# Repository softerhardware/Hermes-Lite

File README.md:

Hermes-Lite 1.x Deprecated Project!!!
=====================================

This project is deprecated. Current development is now focussed on the Hermes-Lite 2.x. See the main [Hermes-Lite Web Page](http://www.hermeslite.com) for the latest links and details.

## Introduction

The hardware is based on Analog Devices' [AD9866](http://www.analog.com/en/broadband-products/broadband-codecs/ad9866/products/product.html) which is a 12-bit broadband modem mixed signal front end that has been repurposed as a direct down conversion and direct up conversion SDR transceiver covering 0-36 MHz. A hardware prototype has been built and tested that uses a [BeMicro SDK](http://www.arrownac.com/solutions/bemicro-sdk/) FPGA board for DSP processing. The FPGA firmware is a port of the [Hermes SDR](http://openhpsdr.org/wiki/index.php?title=HERMES) project. The ported firmware preserves enough compatibility with the original Hermes SDR so that existing Hermes front-end software may be used with the Hermes-Lite without modification. Initial receive and transmit tests show good performance and appear later in this README. All software and hardware intellectual property is open source. Contributions and derivatives are encouraged. Please follow the standard ["Fork and Pull"](https://help.github.com/articles/using-pull-requests/) model and introduce yourself on [Google Groups](https://groups.google.com/forum/#!forum/hermes-lite).

#### Project Goals
 * 0-30MHz (HF) transceiver with decent performance
 * Entirely open source and open hardware design
 * Cost of less than $150 (cost includes FPGA board) for hobbyist who build their own
 * Maintain enough compatibility with Hermes to use existing Hermes SDR front-end software with no or minor modification

#### Hermes-Lite v1.21

#### Hermes-Lite v1.2

#### Hermes-Lite v0.9

## Receive Experiments

I compared the Hermes-Lite with a Hermes and a [SoftRock RXTX Ensemble Transceiver](http://fivedash.com/) at spotting JT65 and JT9 transmissions with [WSJT-X](http://www.physics.princeton.edu/pulsar/K1JT/wsjtx.html) software running on Linux. I connected two radios to the same antenna right at a tee so there is no additional coax for either radio. I adjusted the radios so that common spots are within a few Hz. This ensures that one radio is not spotting signals that are out of band for the other. I adjusted audio levels to be similar for both copies of WSJT-X that I am running. WSJT-X is not very sensitive to different input levels anyway. The Hermes and Hermes-Lite were both using [ghpsdr-alex](http://napan.ca/ghpsdr3/index.php/Main_Page) software running on separate computers, and the RXTX was using [Quisk](http://james.ahlstrom.name/quisk/). The Hermes has a 4-1 impedance transformer. The Hermes-Lite has a 9-1 impedance transformer to better match the 400 Ohm input of the AD9866. This explains some differences in the data. The Hermes was run with no attenuation and hence has 20 dB gain from the LTC6400-20. The Hermes-Lite was also run with integrated gain set to ~20 dB unless noted otherwise. Finally, I let everything run for several hours to get a large sample set. 

### JT65 and JT9 Spot Data

| Band | 30M | 30M | 30M | 10M | 10M | 10M | 10M | 10M |
|:---- | ---:| ---:| ---:| ---:| ---:| ---:| ---:| ---:|
| Total Spots | 1629  |  676  |  826  |  2421  |  1488  |  1934  |  2461  |  570  |
| Common Spots | 1448 (88.9%)  |  647 (95.7%)  |  792 (95.9%)  |  1680 (69.4%)  |  778 (52.3%)  |  1420 (73.4%)  |  1663 (67.6%)  |  414 (72.6%)  |
| Lite Unique Spots |  |  22 (3.3%)  |  24 (2.9%)  |  |  699 (47.0%)  |  493 (25.5%)  |  768 (31.2%)  |  39 (6.8%)  |
| Hermes Unique Spots |  103 (6.3%)  |  7 (1.0%)  |  10 (1.2%)  |  342 (14.1%)  | |  21 (1.1%)  |  30 (1.2%)  |  117 (20.5%)  |
| RXTX Unique Spots |   78 (4.8%)  | | |  399 (16.5%)  |  11 (0.7%)  | | | |
| Lite Gain dB | | 20  | 28  | | 28  | 20  | 28  | 12  |
| Lite Common SNR Average dB |  |  -8.1   |  -7.7   | | -4.7 |  -9.0  |  -9.1   |  -12.8   |
| Hermes Common SNR Average dB | -7.3   |  -8.0   |  -7.7   |  -6.1   | |  -9.8   |  -10.2   |  -9.6   |
| RXTX Common SNR Average dB |  -7.5   | | |  -10.0   |  -12.6   |  | |  |
| Lite Unique SNR Average dB | |  -11.9   |  -11.5   |  |  -17.3   |  -16.2   |  -14.8   |  -15.5   |
| Hermes Unique SNR Average dB |  -15.3   |  -13.3   |  -20.4   |  -16.9   | |  -16.0   |  -14.2   |  -18.5   |
| RXTX Unique SNR Average dB |  -8.6   | | |  -11.9   |  -12.0   | | | |

The results from the Hermes-Lite compare well with the Hermes and the RXTX. You can see that on 30M all radios were about the same, maybe with a slight edge to the Hermes-Lite on unique spot count. The more interesting data is on 10M. Here there was a clear advantage to the Hermes-Lite in terms of unique spots and SNR (average SNR of all common spots) when the Hermes-Lite was run at 20 dB gain (to match the fixed gain of the Hermes but not accounting for the different input transformers) or 28 dB. When the Hermes-Lite was run with only 12 dB gain, the Hermes did better. This suggests that the Hermes might benefit from additional gain on the higher frequencies.  

When one radio has a unique spot that the other misses, it is not because the other radio missed all spots within that minute. Rather, I see that one radio spots n and the other n-1. The missed spot is not always the weakest signal. Sometimes it is a fairly strong signal. More often the missed spot is a JT9 signal, which has a narrower bandwidth and more stringent demands.

I did not experience problems with exceeding the lower dynamic range of the Hermes-Lite. This may be due in part to my relatively poor antenna setup and rural town location. All experiments were with a ~7M vertical with base at ~2M above ground with a wire grape trellis as a ground plane. The vertical was tuned with a Z-match at the base. Also, the integrated gain in the Hermes-Lite with control in 1 dB steps from -12 dB to +48 dB appears useful to extend the dynamic range. There is a fast path to adjust this gain so that an AGC may be implemented.

These experiments only test a receiver's performance at decoding JT65 and JT9 in the real world, and other proper receiver measurments should be run, but I think they are somewhat indicative of a receiver's performance in general. Even though a less expensive ADC and clock source were used when compared to the Hermes, I did not see any dramatic penalty in reception of JT65 and JT9 spots. Instead, I saw cases where the Hermes-Lite performed better. 

## Transmit Experiments

I tested transmit with [WSPR](http://www.physics.princeton.edu/pulsar/K1JT/wspr.html) and observed spots of my signal on [WSPRnet](http://wsprnet.org/). [PowerSDR](http://openhpsdr.org/wiki/index.php?title=PowerSDR) running under Windows was used to test transmit. At first, I had only 10 dBm (10 mW) output as I had not adjusted the transmit interpolation filter for the new sampling frequency. After adjusting the interpolation filter, I had 17 dBm (50 mW) output. I am using the IAMP on the AD9866 which will do 20 dBm (100 mW) and even 23 dBm (200 mW) with some distortion. I am targeting 20 dBm (100 mW) but need to get a large ferrite core to accomodate the correct turns ratio. The unique WSPR spots appear below. This is just an indicator that transmit is working and proper transmit measurments still must be made.

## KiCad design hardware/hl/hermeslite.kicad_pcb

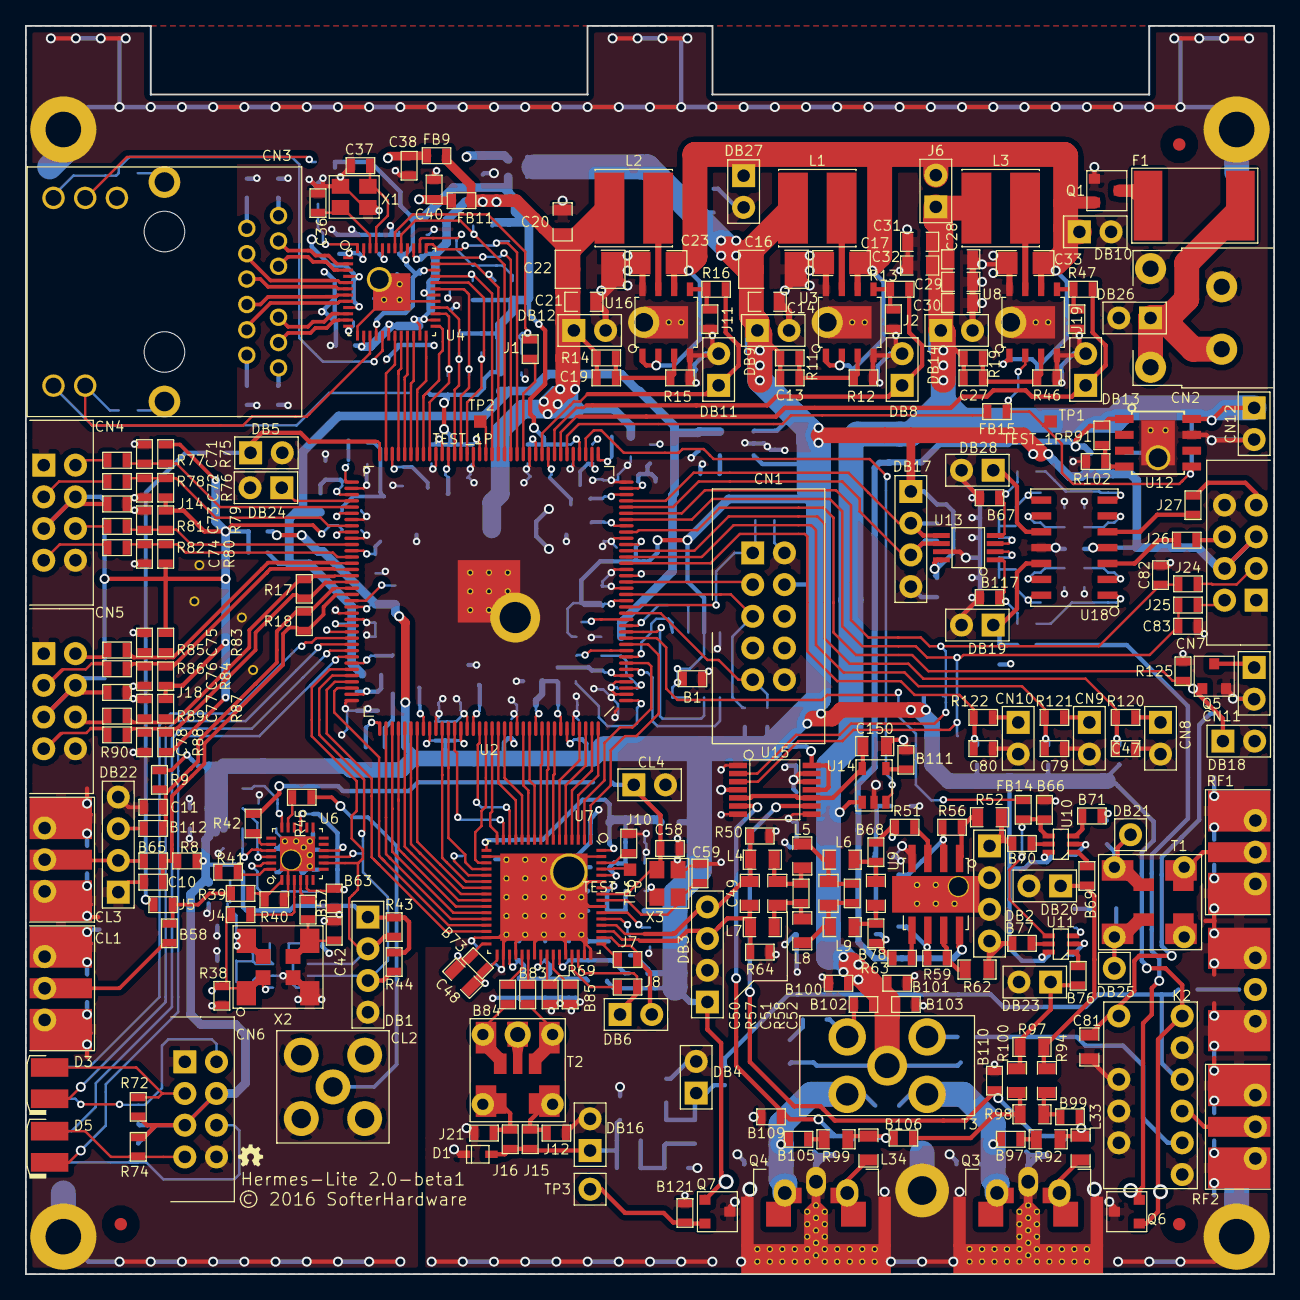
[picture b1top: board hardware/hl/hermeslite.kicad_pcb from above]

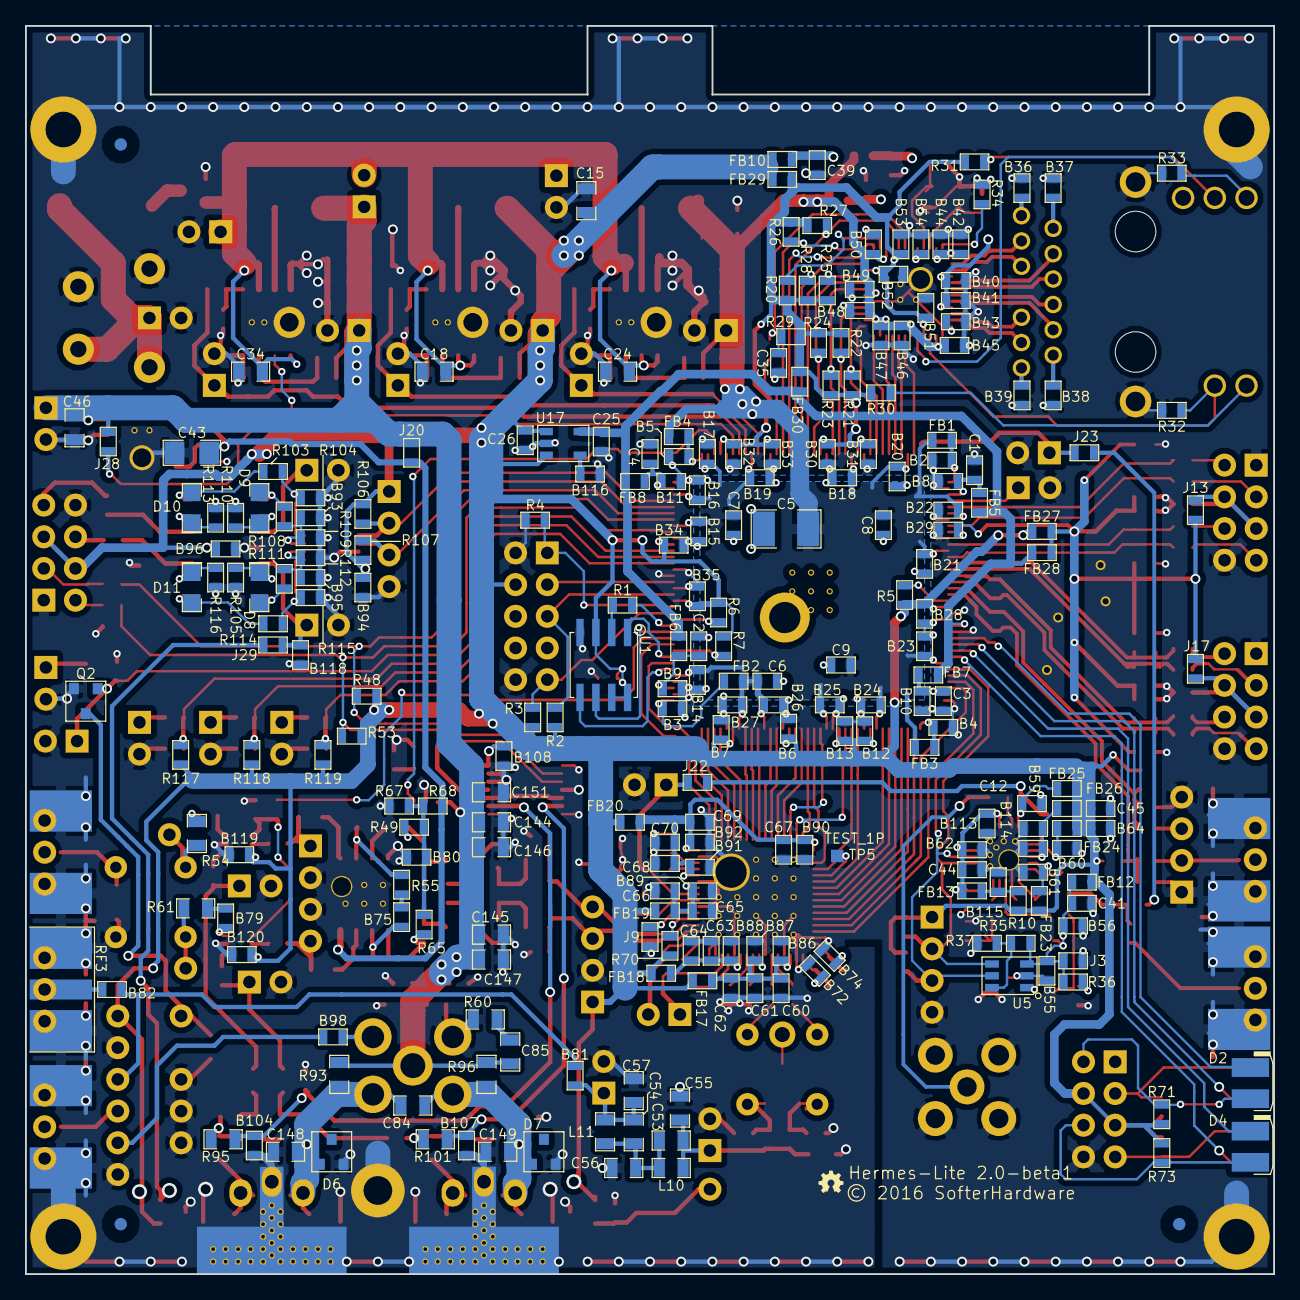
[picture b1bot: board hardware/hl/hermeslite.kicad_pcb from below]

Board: 4 copper layers, 100.0 x 100.0 mm, 514 parts (248 on the bottom side), 289 nets.

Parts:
B1, B2, B3, B4, B5, B6, B7, B8, B9, B10, B11, B12, B13, B14, B15, B16, B17, B18, B19, B20, B21, B22, B23, B24, B25, B26, B27, B28, B29, B30, B31, B32, B33, B34, B35, B36, B37, B38, B39, B40, B41, B42, B43, B44, B45, B46, B47, B48, B49, B50, B51, B52, B53, B54, B55, B56, B57, B58, B59, B60, B61, B62, B63, B64, B65, B66, B67, B68, B69, B70, B71, B72, B73, B74, B75, B76, B77, B78, B79, B80, B81, B82, B83, B84, B85, B86, B87, B88, B89, B90, B91, B92, B93, B94, B95, B96, B97, B98, B99, B100, B101, B102, B103, B104, B105, B106, B107, B108, B109, B110, B111, B112, B113, B114, B115, B116, B117, B119, B120: 0.1uF; SMD-0603
B118, B121: DNI; SMD-0603
C1, C2, C3, C4, C6, C7, C8, C9, C12, C25, C35, C38, C39, C40, C41, C44, C45, C62, C64, C66, C70: 10uF; SMD-0603
C5, C16, C22: 100uF; SMD-1210
C10, C11, C26, C47, C60, C61, C63, C65, C67, C68, C69, C71, C72, C73, C74, C75, C76, C77, C78, C79, C80: 1uF; SMD-0603
C13, C19, C27: 4.7nF; SMD-0603
C14, C15, C20, C21, C28, C29, C30, C31, C32: 22uF; SMD-0805
C17, C23, C33, C43: 10uF; SMD-1206
C18, C24, C34: 4.7uF; SMD-0805
C36, C37, C58, C59: 15pF; SMD-0603
C42, C82, C83: DNI; SMD-0603
C46, C144, C145, C146, C147, C151: 1uF; SMD-0805
C48, C150: 10uF; SMD-0805
C49: 75pF; SMD-0805
C50: 150pF; SMD-0805
C51: 160pF; SMD-0805
C52, C55, C57, C81: 100pF; SMD-0805
C53: 10pF; SMD-0805
C54, C85, C148, C149: DNI; SMD-0805
C56: 180pF; SMD-0805
C84: 270pF; SMD-0805
CL1, CL3: SMA; SMAEDGE_TH
CL2: SMA; SMAVERT
CL4: RFD2b; 2x1
CN1: USBBlaster2; USBBLASTER
CN2: PS; POWERPP
CN3: MagJack; MAGJACK
CN4, CN5, CN6, CN7: IO8; IO
CN8, CN9, CN10, CN11, CN12: RFD2b; 2x1
D1: TVS; SOD323
D2, D3, D4, D5: Led_Small; LED
D6, D7: DNI; SOT23_3
D8, D9, D10, D11: 1N5711; 1N5711WS
DB1, DB2, DB3: RFD4d; 4x1
DB4, DB5, DB16: RFD2a; 2x1
DB6, DB8, DB9, DB10, DB11, DB12, DB13, DB14, DB18, DB19, DB20, DB23, DB24, DB26, DB27, DB28: RFD2b; 2x1
DB17: RFD4b; 4x1
DB21, DB25: TEST_1P; 1x1
DB22: RFD4f; 4x1
F1: 3A@20V; FUSE
FB1, FB2, FB3, FB4, FB5, FB6, FB7, FB8, FB9, FB10, FB11, FB12, FB13, FB14, FB15, FB17, FB18, FB19, FB20, FB23, FB24, FB25, FB26, FB27, FB30: FB; SMD-0603
FB28, FB29: DNI; SMD-0603
FIDUCIAL: VAL**; FIDUCIAL
FIDUCIAL#2, FIDUCIAL#3, FIDUCIAL#4, FIDUCIAL#5, FIDUCIAL#6: VAL**; FIDUCIAL
GT1, GT2, GT3, GT4: TEST_1P; GNDTAP
J1, J2, J9, J10, J11, J14, J15, J18, J19, J20, J21, J22, J24, J25, J26, J27, J29: JNC; SMD-0603
J3, J4, J5, J7, J8, J12, J13, J16, J17, J23, J28: JNO; SMD-0603
J6: DNI; 2x1
K2: NA3WK-K; DPDT_GND
L1, L3: 3.3uH; GENERICPSL
L2: 2.2uH; GENERICPSL
L4, L7: 240nH; SMD-0805
L5, L6, L8, L9: 270nH; SMD-0805
L10, L11: 330nH; SMD-0805
L33, L34: 0nH; SMD-0805
MH1, MH2, MH3, MH4: TEST_1P; m2p5
MH5: TEST_1P; m2p0
Q1: DMP3099L; SOT23_3
Q2: NUD3124; SOT23_3
Q3, Q4: LDMOS; COMBORF
Q5: 2N7002K; SOT23_3
Q6, Q7: MCP9700; SOT23_3
R1, R42, R45, R50, R64: 33; SMD-0603
R2, R3, R4, R5, R6, R7, R8, R9, R15, R21, R22, R23, R24, R25, R27, R28, R29, R37, R70, R75, R76, R79, R80, R83, R84, R87, R88, R117, R118, R119: 10K; SMD-0603
R10: 2.2; SMD-0603
R11: 35.7K; SMD-0603
R12: 11.5K; SMD-0603
R13, R16, R17, R18, R36, R38, R41, R47, R125: DNI; SMD-0603
R14: 20K; SMD-0603
R19: 16.2K; SMD-0603
R20, R26, R49, R65: 2.2K; SMD-0603
R30, R31: 270; SMD-0603
R32, R33, R57, R58, R67, R68, R103, R108, R111, R114: 1K; SMD-0603
R34, R91: 12.1K; SMD-0603
R35: 3.3K; SMD-0603
R39: 120; SMD-0603
R40, R55: 75; SMD-0603
R43, R44, R48, R53, R106, R107: 4.7K; SMD-0603
R46: 1.5K; SMD-0603
R51, R63: 22; SMD-0603
R52, R62: 10; SMD-0805
R54, R61, R94, R100: 14; SMD-0805
R56, R59, R71, R72, R73, R74, R77, R78, R81, R82, R85, R86, R89, R90, R120, R121, R122: 330; SMD-0603
R60, R93, R96, R97, R98: DNI; SMD-0805
R69, R102: 1.6K; SMD-0603
R92, R99: 270; SMD-0805
R95, R101: 1K; SMD-0805
R104, R109, R112, R115: 1.8K; SMD-0603
R105, R110, R113, R116: 220K; SMD-0603
RF1, RF2, RF3: BNC; SMAEDGE_TH
T1: 1:1 Z; TRANSFSMT4
T2: 8:1 Z; TRANSFSMT
T3: TRANSF4CTS; BN202V
TP1, TP2, TP5, TP6: TEST_1P; TP
TP3: TEST_1P; 1x1
U1: EEPROM; SOIC-8
U2: FPGA; CYCLONEIV
U3, U8, U16: ST1S10
U4: KSZ9031RN; KSZ9031
U5: MCP4716
U6: 5P49V5923; IDTVERSA
U7: AD9866BCPZ; AD9866
U9: OPA2677
U10, U11: PE4259
U12: AP2204; ap2204
U13: MAX11613
U14: LP2985; SOT23
U15: MCP4661
U17: TPS730; SOT23
U18: LMV324
X1: 25MHz; XTAL
X2: 38.4MHz; MULTIOSC
X3: 38.4MHz; XTAL

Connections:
+1V2: B14.1, B15.1, B16.1, B17.1, B18.1, B19.1, B20.1, B21.1, B22.1, B23.1, B24.1, B25.1, B26.1, B27.1, B45.1, B46.1, B47.1, B48.1, B49.1, B50.1, C5.2, C6.2, C7.2, C8.2, C9.2, C19.1, C20.1, C21.1, C22.1, DB12.1, FB1.1, FB2.1, FB3.1, FB4.1, FB9.1, FB11.1, L2.2, R14.1, U2.5, U2.29, U2.34, U2.38, U2.45, U2.61, U2.70, U2.78, U2.84, U2.102, U2.116, U2.124, U2.134, U2.138, U4.14, U4.18, U4.23, U4.26, U4.30, U4.39
+2V5: C25.1, FB5.1, FB6.1, FB7.1, FB8.1, FB28.1, FB30.1, U2.96, U17.5
+3V3: B1.1, B6.1, B7.1, B12.1, B13.1, B28.1, B34.1, B35.1, B64.1, B94.1, B96.1, B108.1, B119.1, B120.1, C13.1, C14.1, C15.1, C16.1, C26.1, C45.1, CN1.4, CN6.4, CN6.5, CN7.4, CN7.5, DB1.1, DB3.1, DB9.1, DB17.1, FB10.2, FB12.2, FB17.2, FB18.1, FB19.1, FB20.2, FB23.2, FB24.2, FB25.2, FB26.2, FB27.1, FB29.1, K2.1, L1.2, Q6.1, Q7.1, R2.2, R3.2, R5.2, R6.2, R7.2, R8.2, R9.2, R10.1, R11.1, R43.2, R44.2, R48.2, R53.2, R70.2, R71.2, R72.2, R73.2, R74.2, R106.2, R107.2, R117.2, R118.2, R119.2, U1.3, U1.7, U1.8, U2.17, U2.26, U2.93, U2.117, U2.122, U2.130, U2.139, U10.6, U11.6, U13.8, U15.11, U15.14, U17.1, U17.3, U18.4
+VOP: C43.1, J20.2, R68.2, R91.1, U9.8, U12.1
+VPA: B100.2, B101.2, B102.2, B103.2, C27.1, C28.1, C29.1, C30.1, C31.1, C32.1, C46.1, C85.2, C144.1, C145.1, C146.1, C147.1, C151.1, CN12.1, DB14.1, J6.1, J20.1, J28.1, L3.2, R19.1, R93.1, R96.2, T3.2, U12.8, U14.1
/Clock/SCL1: DB1.3, R44.1, U2.104, U5.5, U6.9
/Clock/SDA1: DB1.2, R43.1, U2.103, U5.4, U6.8
/Ethernet/RXD0: R24.2, U2.58, U4.32
/Ethernet/RXD1: R23.2, U2.59, U4.31
/Ethernet/RXD2: R22.2, U2.60, U4.28
/Ethernet/RXD3: R21.2, U2.64, U4.27
/Ethernet/TXD0: U2.71, U4.19
/Ethernet/TXD1: U2.69, U4.20
/Ethernet/TXD2: U2.68, U4.21
/Ethernet/TXD3: U2.67, U4.22
/Input Output/AIN1: J26.1, U18.3
/Input Output/AIN2: J27.1, U18.5
/PA/TR: DB18.1, Q2.1, Q5.1, R125.2, U2.28
/PA/bias0: B104.2, B110.1, R95.2, U15.9
/PA/bias1: B107.2, B109.1, R101.2, U15.6
/RF Frontend/Vop/2: B80.2, R49.1, R65.2, R67.2, R68.1
GND: B1.2, B2.2, B3.2, B4.2, B5.2, B6.2, B7.2, B8.2, B9.2, B10.2, B11.2, B12.2, B13.2, B14.2, B15.2, B16.2, B17.2, B18.2, B19.2, B20.2, B21.2, B22.2, B23.2, B24.2, B25.2, B26.2, B27.2, B28.2, B29.2, B30.2, B31.2, B32.2, B33.2, B34.2, B35.2, B36.2, B37.2, B38.2, B39.2, B40.2, B41.2, B42.2, B43.2, B44.2, B45.2, B46.2, B47.2, B48.2, B49.2, B50.2, B51.2, B52.2, B53.2, B54.2, B55.2, B56.2, B59.2, B60.2, B61.2, B62.2, B63.2, B64.2, B66.1, B67.2, B72.2, B74.2, B80.1, B85.2, B86.2, B87.2, B88.2, B89.2, B90.2, B91.2, B92.2, B93.2, B94.2, B95.2, B96.2, B100.1, B101.1, B102.1, B103.1, B104.1, B107.1, B108.2, B109.2, B110.2, B111.2, B113.2, B114.2, B115.2, B116.2, B117.2, B118.2, B119.2, B120.2, B121.2, C1.2, C2.2, C3.2, C4.2, C5.1, C6.1, C7.1, C8.1, C9.1, C10.2, C11.2, C12.2, C14.2, C15.2, C16.2, C17.2, C18.2, C20.2, C21.2, C22.2, C23.2, C24.2, C25.2, C26.2, C28.2, C29.2, C30.2, C31.2, C32.2, C33.2, C34.2, C35.2, C36.2, C37.2, C38.2, C39.2, C40.2, C41.2, C42.1, C43.2, C44.2, C45.2, C46.2, C47.2, C55.2, C56.2, C57.2, C58.2, C59.2, C60.2, C61.2, C62.2, C63.2, C64.2, C65.2, C66.2, C67.2, C68.2, C69.2, C70.2, C71.2, C72.2, C73.2, C74.2, C75.2, C76.2, C77.2, C78.2, C79.2, C80.2, C81.2, C82.2, C83.2, C144.2, C145.2, C146.2, C147.2, C148.2, C149.2, C150.2, C151.2, CL1.2, CL2.2, CL3.2, CL4.2, CN1.2, CN1.10, CN2.2, CN3.18, CN4.1, CN4.8, CN5.1, CN5.8, CN6.1, CN6.8, CN7.1, CN7.8, CN8.2, CN9.2, CN10.2, CN11.2, CN12.2, D1.2, D6.2, D7.2, DB1.4, DB2.2, DB2.3, DB3.2, DB4.2, DB5.2, DB8.2, DB9.2, DB10.2, DB11.2, DB12.2, DB13.2, DB14.2, DB16.2, DB17.4, DB18.2, DB19.2, DB20.2, DB22.1, DB22.4, DB23.2, DB24.2, DB26.2, DB27.2, DB28.2, GT1.1, GT2.1, GT3.1, GT4.1, J2.1, J3.2, J9.1, J10.1, J11.1, J12.2, J14.1, J18.1, J19.1, J21.1, K2.2, K2.6, K2.8, K2.9, K2.10, MH1.1, MH2.1, MH3.1, MH4.1, MH5.1, Q1.1, Q2.2, Q3.2, Q4.2, Q5.2, Q6.3, Q7.3, R4.2, R12.2, R15.2, R32.2, R33.2, R34.2, R37.2, R38.2, R40.2, R46.2, R50.2, R60.1, R64.1, R67.1, R69.1, R102.1, R104.1, R105.2, R109.1, R110.2, R112.1, R113.2, R115.1, R116.2, R125.1, RF1.2, RF2.2, RF3.2, T1.3, T3.4, U1.4, U2.2, U2.4, U2.19, U2.21, U2.22, U2.27, U2.36, U2.41, U2.48, U2.57, U2.63, U2.74, U2.79, U2.82, U2.94, U2.95, U2.97, U2.108, U2.118, U2.123, U2.131, U2.140, U2.145, U3.4, U3.8, U3.9, U4.13, U4.29, U4.49, U5.2, U6.2, U6.25, U7.18, U7.31, U7.34, U7.36, U7.39, U7.44, U7.47, U7.48, U7.55, U7.59, U7.63, U7.65, U8.4, U8.8, U8.9, U9.4, U10.2, U11.2, U12.7, U13.7, U14.2, U15.1, U15.4, U15.7, U15.8, U15.12, U15.13, U16.4, U16.8, U16.9, U17.2, U18.11, X1.3, X2.2, X3.3
unnamed: B2.1, FB1.2, U2.73
unnamed: B3.1, FB2.2, U2.1
unnamed: B4.1, FB3.2, U2.109
unnamed: B5.1, FB4.2, U2.37
unnamed: B8.1, C1.1, FB5.2, U2.75
unnamed: B9.1, C2.1, FB6.2, U2.3
unnamed: B10.1, C3.1, FB7.2, U2.107
unnamed: B11.1, C4.1, FB8.2, U2.35
unnamed: B36.1, CN3.12
unnamed: B37.1, CN3.6
unnamed: B38.1, CN3.1
unnamed: B39.1, CN3.7
unnamed: B40.1, B41.1, C38.1, FB9.2, U4.4, U4.9
unnamed: B42.1, B43.1, B44.1, C39.1, FB10.1, U4.1, U4.12, U4.47
unnamed: B54.1, C40.1, FB11.2, U4.44
unnamed: B55.1, B56.1, C41.1, FB12.1, J3.1, R35.1, R36.1, U5.3, X2.4
unnamed: B57.1, C42.2, X2.3
unnamed: B57.2, U6.4
unnamed: B58.1, J5.1, R39.2
unnamed: B58.2, CL1.1
unnamed: B59.1, FB25.1, U6.18
unnamed: B60.1, FB24.1, U6.21
unnamed: B61.1, FB23.1, U6.23
unnamed: B65.1, CL3.1, DB22.2
unnamed: B65.2, C10.1, R8.1, R18.1, U2.91
unnamed: B66.2, FB14.1, U10.4, U11.4
unnamed: B67.1, R103.1, R104.2, U13.4
unnamed: B68.1, R49.2, R51.2
unnamed: B68.2, C52.1, L6.2
unnamed: B69.1, U10.1
unnamed: B70.1, U10.5
unnamed: B70.2, DB2.1, R52.1
unnamed: B71.1, U10.3
unnamed: B71.2, R54.2
unnamed: B72.1, B73.1, C48.1, U7.33
unnamed: B73.2, B74.1, C48.2, U7.32
unnamed: B75.1, R59.2, U9.6
unnamed: B75.2, R55.1
unnamed: B76.1, U11.1
unnamed: B77.1, U11.5
unnamed: B77.2, DB2.4, R62.1
unnamed: B78.1, R63.2, R65.1
unnamed: B78.2, C52.2, L9.1
unnamed: B79.1, U11.3
unnamed: B79.2, R61.2
unnamed: B81.2, C54.1, C57.1, DB4.1, L11.2
unnamed: B82.1, RF3.1
unnamed: B83.1, T2.1
unnamed: B83.2, U7.38
unnamed: B84.1, T2.3
unnamed: B84.2, U7.37
unnamed: B85.1, U7.42
unnamed: B86.1, B87.1, C60.1, C61.1, C62.1, FB17.1, U7.35, U7.40
unnamed: B88.1, C63.1, C64.1, FB18.2, U7.43
unnamed: B89.1, C65.1, C66.1, FB19.2, U7.58
unnamed: B90.1, B91.1, B92.1, C67.1, C68.1, C69.1, C70.1, FB20.1, U7.17, U7.60, U7.64
unnamed: B93.1, R108.1, R109.2, U13.3
unnamed: B95.1, R111.1, R112.2, U13.2
unnamed: B97.1, C84.1, C148.1, D6.1, Q3.3, R93.2, T3.1
unnamed: B97.2, R92.1
unnamed: B98.1, K2.5
unnamed: B98.2, T3.5
unnamed: B99.1, L33.1, R92.2, R95.1
unnamed: B99.2, R94.1, R98.2
unnamed: B105.1, C84.2, C149.1, D7.1, Q4.3, R96.1, T3.3
unnamed: B105.2, R99.1
unnamed: B106.1, L34.1, R99.2, R101.1
unnamed: B106.2, R98.1, R100.1
unnamed: B111.1, U14.4
unnamed: B112.1, DB22.3
unnamed: B112.2, C11.1, R9.1, R18.2, U2.90
unnamed: B62.1, B63.1, B113.1, C44.1, FB13.1, U6.5, U6.10, U6.15
unnamed: B114.1, C12.1, FB26.1, U6.22
unnamed: B115.1, FB13.2, R10.2
unnamed: B116.1, U17.4
unnamed: B117.1, R114.1, R115.2, U13.1
unnamed: B118.1, DB19.1, J29.2, U18.12
unnamed: B121.1, Q7.2, TP3.1
unnamed: C13.2, R11.2, R12.1, U3.3
unnamed: C17.1, C18.1, C23.1, C24.1, C33.1, C34.1, DB10.1, DB27.1, J6.2, Q1.2, U3.1, U3.2, U3.6, U8.1, U8.6, U16.1, U16.2, U16.6
unnamed: C19.2, R14.2, R15.1, U16.3
unnamed: C27.2, R19.2, R46.1, U8.3
unnamed: C35.1, J1.1, R29.1, U4.42
unnamed: C36.1, U4.46, X1.2
unnamed: C37.1, U4.45, X1.1
unnamed: C47.1, R117.1, R120.2, U2.25
unnamed: C49.1, DB3.4, L4.1, R50.1, U7.52
unnamed: C49.2, DB3.3, L7.2, R64.2, U7.51
unnamed: C50.1, L4.2, L5.1, R57.2
unnamed: C50.2, L7.1, L8.2, R57.1
unnamed: C51.1, L5.2, L6.1, R58.2
unnamed: C51.2, L8.1, L9.2, R58.1
unnamed: C53.1, C54.2, C56.1, L10.2, L11.1
unnamed: C53.2, C55.1, D1.1, DB16.1, J15.2, J16.1, L10.1
unnamed: C58.1, CL4.1, J22.2, U7.57, X3.2
unnamed: C59.1, U7.56, X3.1
unnamed: C71.1, R75.1, R77.1, U2.77
unnamed: C72.1, R76.1, R78.1, U2.80
unnamed: C73.1, R79.1, R81.1, U2.83
unnamed: C74.1, R80.1, R82.1, U2.85
unnamed: C75.1, R83.1, R85.1, U2.86
unnamed: C76.1, R84.1, R86.1, U2.87
unnamed: C77.1, R17.1, R87.1, R89.1, U2.88
unnamed: C78.1, R17.2, R88.1, R90.1, U2.89
unnamed: C79.1, R118.1, R121.2, U2.24
unnamed: C80.1, R119.1, R122.2, U2.23
unnamed: C81.1, K2.12, Q2.3
unnamed: C85.1, R60.2
unnamed: C150.1, U14.5, U15.5, U15.10
unnamed: CL2.1, R45.1
unnamed: CN1.1, R4.1, U2.16
unnamed: CN1.3, U2.20
unnamed: CN1.5, R2.1, U2.18
unnamed: CN1.9, R3.1, U2.15
unnamed: CN2.1, DB26.1, F1.1
unnamed: CN3.2, U4.8
unnamed: CN3.3, U4.7
unnamed: CN3.4, U4.6
unnamed: CN3.5, U4.5
unnamed: CN3.8, U4.11
unnamed: CN3.9, U4.10
unnamed: CN3.10, U4.3
unnamed: CN3.11, U4.2
unnamed: CN3.13, R32.1, U4.15
unnamed: CN3.14, R30.1
unnamed: CN3.16, R31.1
unnamed: CN3.17, R33.1, U4.17
unnamed: CN4.2, R77.2
unnamed: CN4.3, R78.2
unnamed: CN4.4, CN4.5, J13.2, J14.2
unnamed: CN4.6, R81.2
unnamed: CN4.7, R82.2
unnamed: CN5.2, R85.2
unnamed: CN5.3, R86.2
unnamed: CN5.4, CN5.5, J17.2, J18.2
unnamed: CN5.6, R89.2
unnamed: CN5.7, R90.2
unnamed: CN6.2, D2.2, R71.1
unnamed: CN6.3, D3.2, R72.1
unnamed: CN6.6, D4.2, R73.1
unnamed: CN6.7, D5.2, R74.1
unnamed: CN7.2, J25.2
unnamed: CN7.3, J24.2
unnamed: CN7.6, J26.2
unnamed: CN7.7, J27.2
unnamed: CN8.1, R120.1
unnamed: CN9.1, R121.1
unnamed: CN10.1, R122.1
unnamed: CN11.1, Q5.3
unnamed: D2.1, U2.98
unnamed: D3.1, U2.99
unnamed: D4.1, U2.100
unnamed: D5.1, U2.101
unnamed: D8.1, R111.2, U18.14
unnamed: D8.2, R105.1, U18.13
unnamed: D9.1, R108.2, U18.8
unnamed: D9.2, R110.1, U18.9
unnamed: D10.1, R103.2, U18.7
unnamed: D10.2, R113.1, U18.6
unnamed: D11.1, R114.2, U18.1
unnamed: D11.2, R116.1, U18.2
unnamed: DB5.1, J23.2, U2.72
unnamed: DB6.1, J8.1, U7.46
unnamed: DB6.2, J7.1, U7.50
unnamed: DB8.1, R13.2, U2.44
unnamed: DB11.1, R16.2, U2.46
unnamed: DB13.1, R47.2, U2.43
unnamed: DB17.2, R106.1, U2.33, U13.5
unnamed: DB17.3, R107.1, U2.32, U13.6
unnamed: DB21.1, R54.1, T1.1
unnamed: DB24.1, U2.76
unnamed: DB25.1, R61.1, T1.2
unnamed: DB28.1, U18.10
unnamed: F1.2, Q1.3
unnamed: FB14.2, U2.11
unnamed: FB15.1, U2.42
unnamed: FB15.2, J28.2, TP1.1, U8.2, U12.5
unnamed: J1.2, U2.49
unnamed: J2.2, R13.1, U3.5
unnamed: J4.1, R36.2, R38.1, U5.1, X2.1
unnamed: J4.2, U6.3
unnamed: J7.2, U7.49
unnamed: J8.2, U7.45
unnamed: J9.2, U7.54
unnamed: J10.2, U7.62
unnamed: J11.2, R16.1, U16.5
unnamed: J12.1, J15.1, T2.5
unnamed: J16.2, J21.2, T2.4
unnamed: J19.2, R47.1, U8.5
unnamed: J5.2, J23.1
unnamed: J29.1, Q6.2
unnamed: K2.4, RF2.1
unnamed: L1.1, U3.7
unnamed: L2.1, U16.7
unnamed: L3.1, U8.7
unnamed: L33.2, Q3.1
unnamed: L34.2, Q4.1
unnamed: R1.1, U1.2
unnamed: R1.2, U2.13
unnamed: R5.1, U2.92
unnamed: R6.1, U2.14
unnamed: R7.1, U2.9
unnamed: R20.2, U4.38
unnamed: R25.2, U2.54, U4.33
unnamed: R26.2, U2.50, U4.37
unnamed: R27.1, U2.52, U4.41
unnamed: R28.1, U2.53, U4.35
unnamed: R34.1, U4.48
unnamed: R35.2, R37.1, U5.6
unnamed: R39.1, R40.1, U6.1
unnamed: R41.2, U6.24
unnamed: R42.2, U6.20
unnamed: R45.2, U6.17
unnamed: R51.1, U9.3
unnamed: R52.2, R56.1, U9.1
unnamed: R55.2, R56.2, U9.2
unnamed: R59.1, R62.2, U9.7
unnamed: R63.1, U9.5
unnamed: R69.2, U7.41
unnamed: R70.1, U7.53
unnamed: R91.2, R102.2, U12.4
unnamed: RF1.1, T1.4
unnamed: TP2.1, U2.55
unnamed: TP5.1, U7.21
unnamed: TP6.1, U7.61
unnamed: U1.1, U2.8
unnamed: U1.5, U2.6
unnamed: U1.6, U2.12
unnamed: U2.7, U7.2
unnamed: U2.10, U7.1
unnamed: U2.51, U4.36
unnamed: U2.65, U4.25
unnamed: U2.66, U4.24
unnamed: U2.105, U7.30
unnamed: U2.106, U7.29
unnamed: U2.110, U7.28
unnamed: U2.111, U7.27
unnamed: U2.112, U7.26
unnamed: U2.113, U7.25
unnamed: U2.114, U7.24
unnamed: U2.115, U7.23
unnamed: U2.119, U7.22
unnamed: U2.120, U7.20
unnamed: U2.121, U7.15
unnamed: U2.125, U7.14
unnamed: U2.126, U7.19
unnamed: U2.127, U7.16
unnamed: U2.128, U7.13
unnamed: U2.129, U7.12
unnamed: U2.132, U7.11
unnamed: U2.133, U7.10
unnamed: U2.135, U7.9
unnamed: U2.136, U7.8
unnamed: U2.137, U7.7
unnamed: U2.141, U7.6
unnamed: U2.142, U7.5
unnamed: U2.143, U7.4
unnamed: U2.144, U7.3
unnamed: U2.39, U14.3
PATRRX: B81.1, B82.2, K2.3
RFFE_CLK: J22.1, R42.1
SCL2: C82.1, J24.1, R48.1, U2.31, U15.2
SDA2: C83.1, J25.1, R53.1, U2.30, U15.3
TXPAn: B76.2, DB23.1, R97.1, R100.2
TXPAp: B69.2, DB20.1, R94.2, R97.2
Veth: B30.1, B31.1, B32.1, B33.1, B51.1, B52.1, B53.1, FB29.2, FB30.2, R20.1, R21.1, R22.1, R23.1, R24.1, R25.1, R26.1, R27.2, R28.2, R29.2, R30.2, R31.2, U2.40, U2.47, U2.56, U2.62, U4.16, U4.34, U4.40
Vlvds: B29.1, FB27.2, FB28.2, J13.1, J17.1, R75.2, R76.2, R79.2, R80.2, R83.2, R84.2, R87.2, R88.2, U2.81

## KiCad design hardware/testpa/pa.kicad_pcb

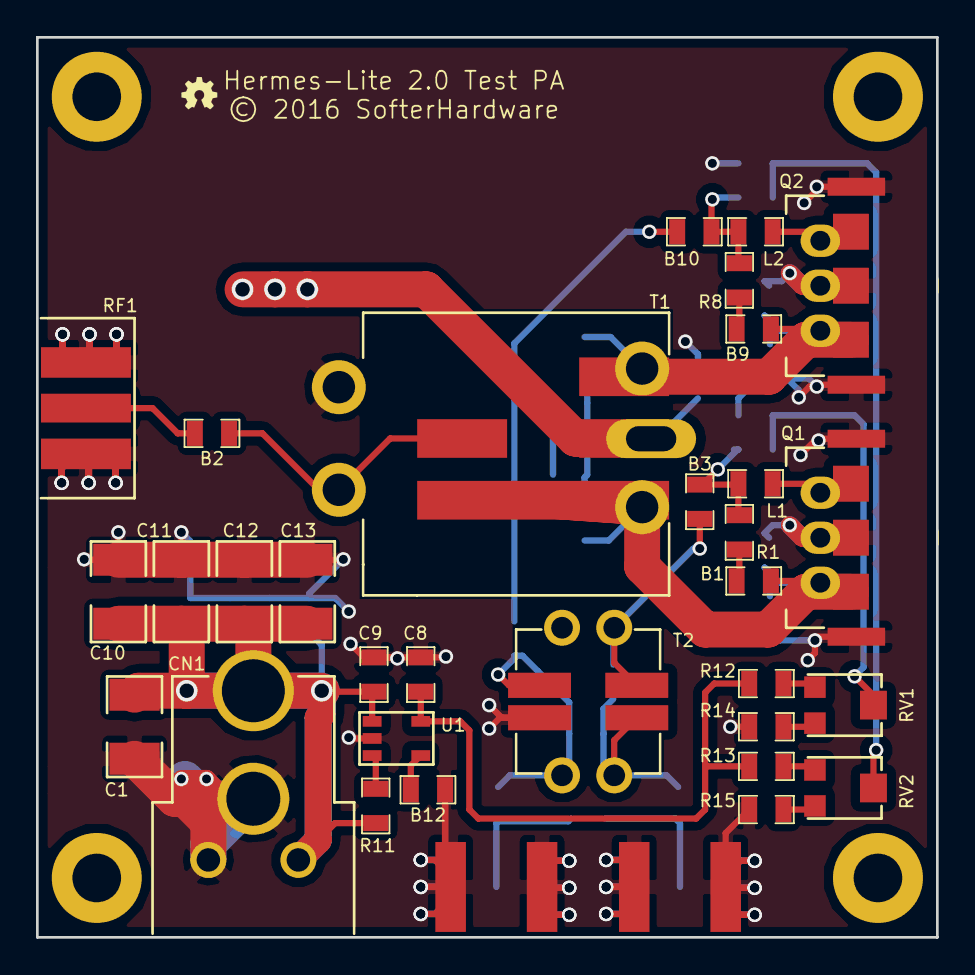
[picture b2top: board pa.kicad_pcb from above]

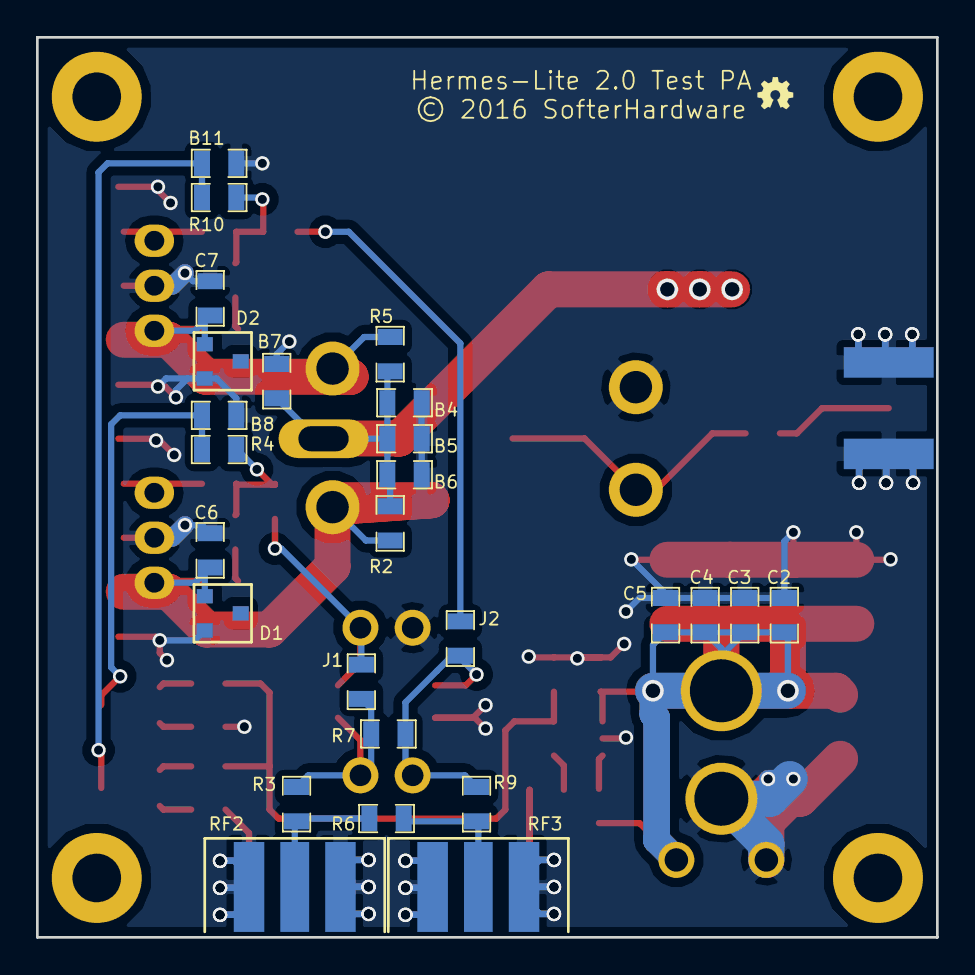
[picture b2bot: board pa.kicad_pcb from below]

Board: 4 copper layers, 50.0 x 50.0 mm, 61 parts (26 on the bottom side), 27 nets.

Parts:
B1, B2, B3, B4, B5, B6, B7, B8, B9, B10, B11, B12: 0.1uF; SMD-0805
C1, C10, C11, C12, C13: 22uF; SMD-1210
C2, C3, C4, C5, C9: 1uF; SMD-0805
C6, C7: DNI; SMD-0805
C8: 10uF; SMD-0805
CN1: CONN_01X02; POWER
D1, D2: DNI; SOT23_3
J1, J2: JNC; SMD-0805
L1, L2: 100nH; SMD-0805
MH: VAL**; MH_small
MH#2, MH#3, MH#4: VAL**; MH_small
Q1, Q2: LDMOS; MITSUBISHI
R1, R8: 270; SMD-0805
R2, R5, R6, R7: DNI; SMD-0805
R3, R9: 10; SMD-0805
R4, R10: 1K; SMD-0805
R11: 10K; SMD-0805
R12, R13, R14, R15: 0; SMD-0805
RF1, RF2, RF3: SMA; SMAEDGE
RV1, RV2: 1K; TC33X-2-102E
T1: TRANSF4CTS; TPATX
T2: 1:1 Z; T1_1LP
U1: LP2985; SOT23

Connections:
/Vpa: B4.2, B5.2, B6.2, B7.2, C1.1, C2.1, C3.1, C4.1, C5.1, C9.1, C10.1, C11.1, C12.1, C13.1, CN1.1, R2.1, R5.2, R11.2, T1.2, U1.1
/bias0: B8.2, R4.2, RV1.2
/bias1: B11.2, R10.2, RV2.2
GND: B4.1, B5.1, B6.1, B7.1, B8.1, B11.1, B12.2, C1.2, C2.2, C3.2, C4.2, C5.2, C6.2, C7.2, C8.2, C9.2, C10.2, C11.2, C12.2, C13.2, CN1.2, D1.2, D2.2, Q1.2, Q2.2, R14.1, R15.1, RF1.2, RF2.2, RF3.2, T1.4, T2.3, U1.2
unnamed: B1.1, C6.1, D1.1, Q1.3, R2.2, T1.1
unnamed: B1.2, R1.1
unnamed: B2.1, RF1.1
unnamed: B2.2, T1.5
unnamed: B3.1, L1.1, R1.2, R4.1
unnamed: B3.2, J1.1, T2.4
unnamed: B9.1, C7.1, D2.1, Q2.3, R5.1, T1.3
unnamed: B9.2, R8.1
unnamed: B10.1, L2.1, R8.2, R10.1
unnamed: B10.2, J2.1
unnamed: B12.1, U1.4
unnamed: C8.1, R12.2, R13.2, U1.5
unnamed: J1.2, R3.1, R7.2, T2.1
unnamed: J2.2, R7.1, R9.1, T2.2
unnamed: L1.2, Q1.1
unnamed: L2.2, Q2.1
unnamed: R3.2, R6.2, RF2.1
unnamed: R6.1, R9.2, RF3.1
unnamed: R11.1, U1.3
unnamed: R12.1, RV1.1
unnamed: R13.1, RV2.1
unnamed: R14.2, RV1.3
unnamed: R15.2, RV2.3

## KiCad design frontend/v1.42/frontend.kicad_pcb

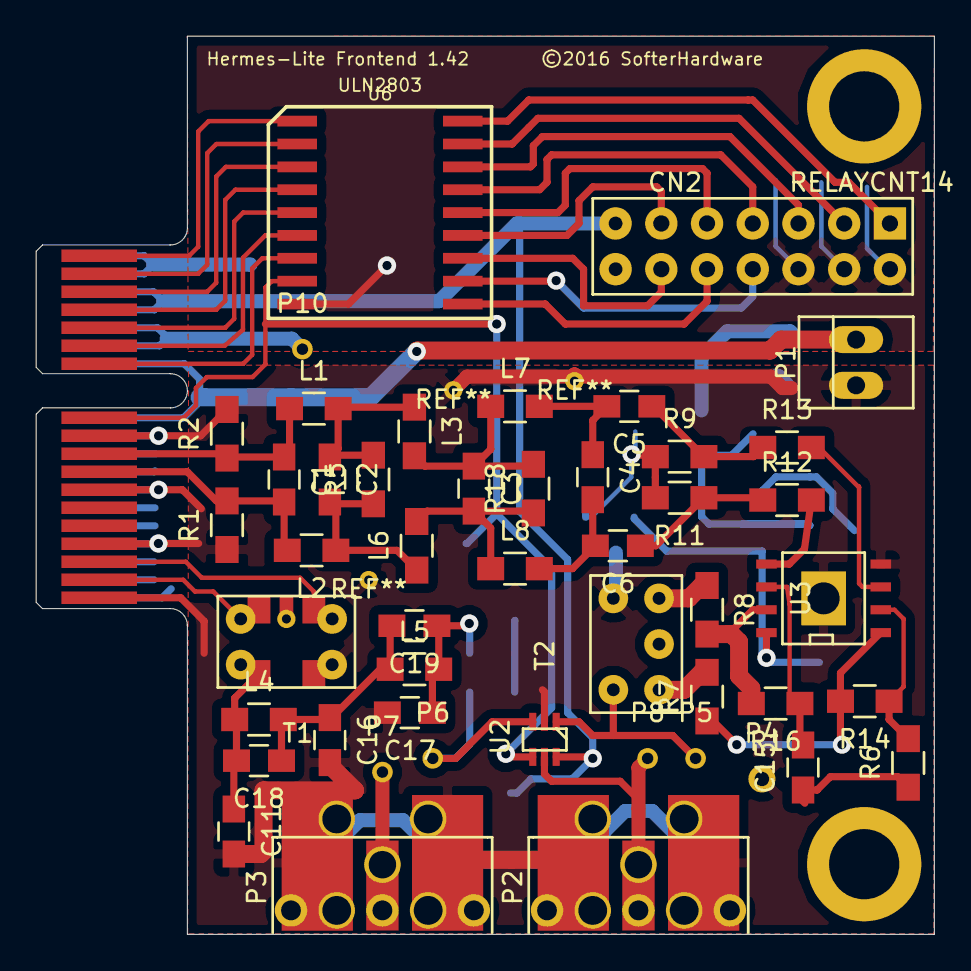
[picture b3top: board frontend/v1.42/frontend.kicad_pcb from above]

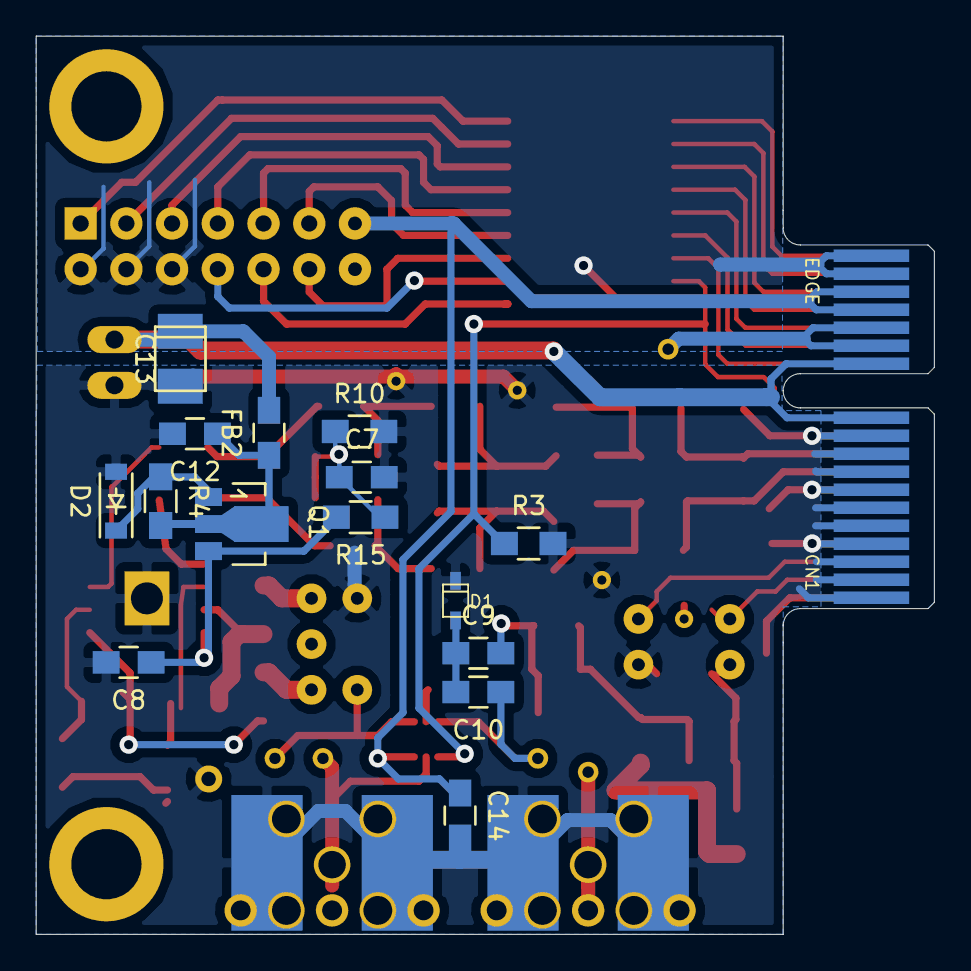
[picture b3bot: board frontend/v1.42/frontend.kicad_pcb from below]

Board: 2 copper layers, 49.9 x 49.9 mm, 66 parts (16 on the bottom side), 55 nets.

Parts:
C1: 75p; C_0805_HandSoldering
C2: 150p; C_0805_HandSoldering
C3: 160p; C_0805_HandSoldering
C4, C11, C17: 100p; C_0805_HandSoldering
C5, C6, C7, C8, C9, C10, C12, C14, C15: 100n; C_0805_HandSoldering
C13: 10u; TantalC_SizeT_EIA-3528
C16: 180p; C_0805_HandSoldering
C18, C19: zero; C_0805_HandSoldering
CN1: EDGE
CN2: RELAYCNT14; BREAKOUT14
D1: DIODESCH2; SOD323
D2: BZT52B12; SOD-123
FB2: FB; C_0805_HandSoldering
L1, L2: 240n; R_0805_HandSoldering
L3, L6, L7, L8: 270n; R_0805_HandSoldering
L4, L5: 330n; R_0805_HandSoldering
MH: VAL**; MH
MH#2: VAL**; MH
P1: 12V; PINHEAD1-2
P2, P3: SMA/BNC/HDR; rfconnectorB
P4, P5, P6, P7, P8, P10: TST; Measurement_Point_Round-TH_Small
Q1: FCX690B; SOT89-3_Housing
R1, R2: 33 1%; R_0805_HandSoldering
R3: 10k; R_0805_HandSoldering
R4: 560; R_0805_HandSoldering
R5, R18: 1000; R_0805_HandSoldering
R6: 75 1%; R_0805_HandSoldering
R7, R8: 24 1/4W; R_0805_HandSoldering
R9, R11: 2200; R_0805_HandSoldering
R10, R15: 1200; R_0805_HandSoldering
R12, R13: 22; R_0805_HandSoldering
R14, R16: 330 1%; R_0805_HandSoldering
T1: 8:1Z; TransfBN2402
T2: 1:1; TransfBN2402
U2: PE4259; pe4259
U3: OPA2674; SOIC-8-N-PAD
U6: ULN2803; PSOP-18

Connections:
3V: C14.1, CN1.A15, CN1.A16, CN2.13, U2.6
5V: CN1.A13, CN1.A14, P10.1
10V: C8.1, Q1.3, R15.2, U3.8
12V: C13.1, CN1.A11, CN1.A12, FB2.2, P1.2
GND: C7.2, C8.2, C11.2, C12.2, C13.2, C14.2, C16.2, C17.2, CN1.A1, CN1.A2, CN1.A3, CN1.A4, CN1.A5, CN1.A6, CN1.A7, CN1.A8, CN1.A9, CN1.A10, CN1.B1, CN1.B4, CN1.B7, CN1.B10, D1.2, D2.2, P1.1, P2.2, P3.2, P4.1, R1.1, R2.2, R3.2, R10.2, T1.6, T2.4, U2.2, U3.4
GNDREF: CN1.A17, CN1.A18, CN2.2, CN2.4, CN2.6, U6.9
unnamed: C1.1, CN1.B9, L1.1, R2.1
unnamed: C1.2, CN1.B8, L2.2, R1.2
unnamed: C2.1, L1.2, L3.1, R5.2
unnamed: C2.2, L2.1, L6.1, R5.1
unnamed: C3.1, L3.2, L7.1, R18.2
unnamed: C3.2, L6.2, L8.1, R18.1
unnamed: C4.1, C5.2, L7.2
unnamed: C4.2, C6.2, L8.2
unnamed: C5.1, R9.2, R13.1
unnamed: C6.1, R11.1, R12.1
unnamed: C7.1, R9.1, R10.1, R11.2, R15.1
unnamed: C10.1, P6.1, U2.3
unnamed: C9.1, C10.2, D1.1
unnamed: C11.1, C18.2, L4.1, T1.4
unnamed: C12.1, FB2.1, Q1.2, R4.2
unnamed: C15.1, R6.1
unnamed: C15.2, R16.1, U3.6
unnamed: C16.1, C18.1, C19.2, L4.2, L5.1
unnamed: C9.2, C17.1, C19.1, L5.2
unnamed: CN1.B2, T1.3
unnamed: CN1.B3, T1.1
unnamed: CN1.B11, R3.1, U2.4, U6.8
unnamed: CN1.B12, U6.7
unnamed: CN1.B13, U6.6
unnamed: CN1.B14, U6.5
unnamed: CN1.B15, U6.4
unnamed: CN1.B16, U6.3
unnamed: CN1.B17, U6.2
unnamed: CN1.B18, U6.1
unnamed: CN2.1, U6.18
unnamed: CN2.3, U6.17
unnamed: CN2.5, U6.16
unnamed: CN2.7, U6.15
unnamed: CN2.8, U6.11
unnamed: CN2.9, U6.14
unnamed: CN2.10, U6.10
unnamed: CN2.11, U6.13
unnamed: CN2.12, U6.12
unnamed: D2.1, Q1.1, R4.1
unnamed: P2.1, P8.1, U2.5
unnamed: P3.1, P7.1
unnamed: P5.1, T2.6, U2.1
unnamed: R7.2, T2.1
unnamed: R8.1, T2.3
unnamed: R12.2, U3.5
unnamed: R13.2, U3.3
unnamed: R6.2, R14.1, U3.2
unnamed: R7.1, R14.2, U3.1
unnamed: R8.2, R16.2, U3.7

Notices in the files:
frontend/v1.25/frontend.kicad_pcb:
©2015 SofterHardware
frontend/v1.42/frontend.kicad_pcb:
©2016 SofterHardware
pcb/ad9866.kicad_pcb:
Copyright 2014
